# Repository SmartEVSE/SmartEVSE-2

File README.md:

SmartEVSE
=========

Smart Electric Vehicle Charge Controller

# What is it?

It's a open source EVSE (Electric Vehicle Supply Equipment). It supports 1-3 phase charging, fixed charging cable or charging socket. Locking actuator support (3 different types). And it can directly drive a mains contactor for supplying power to the EV. It features a display from which all module parameters can be configured.<br>
Up to 8 modules can be connected together to charge up to eight EV's from one mains connection without overloading it.<br>
The mains connection can be monitored by the (optional) sensorbox or a modbus kWh meter. This allows smart charging.
Communication between the SmartEVSE(s) / Sensorbox or kWh meters is done over RS485(modbus).

The project consists of two parts:
- Smart EVSE controller
- Sensorbox

# Features

- Fits into a standard DIN rail enclosure.
- Measures the current consumption of other appliances, and automatically lowers or increases the charging current to the EV. (sensorbox required)
- The load balancing feature let's you connect up to 8 SmartEVSE's to one mains supply.
- Switched 230VAC output, for contactor/relay.
- Powered RS485 communication bus for sensorbox / Modbus kWh Meters.
- Can be used with fixed cable, or socket and charging cable.
- Automatically selects current capacity of the connected cable (13/16/32A)
- Locking actuator support, locks the charging cable in the socket, automatically unlocks on a power failure.
- RFID reader support, restrict the use of the charging station to max 20 RFID cards.
- An optional modbus kWh meter will measure power and charged energy, and display this on the LCD.
- Built-in temperature sensor.
- All module parameters can be configured using the display and buttons.
- Setup can also be done through serial CLI.
- Firmware upgradable through serial bootloader. 

New V2.20 features are:
- Added EVMETER and EVADR option to the menu. Use a modbus kWh meter to measure the charged energy.
- Added charged energy to the LCD (Smart/Solar mode)
- Uses condensed characters on the LCD, so the 'i' will not use the same space as the 'w'
- Increased the nr of nodes to 7.
- Added RFID reader option. Learn up to 20 RFID cards.

# The Sensorbox

The Sensorbox should be placed where the Mains connection enters the building. Usually just after the kWh meter, this way it will be able to measure the total current per phase and send this information to the SmartEVSE.

In order to measure the current, Current transformers are used. Clip them around the L1,L2 and L3 wires, and plug the other end into the sensorbox.

# Configuring the SmartEVSE

The SmartEVSE has a display, which shows the charging status, and if smart mode is used, also the measured current per phase.
It is possible to configure all settings using the built-in menu.

Three buttons below the display are used for navigating the menu.

Hold the center button for 2 seconds to enter the menu.
You can now use the left and right buttons to go to the different menu options. 

Pressing the center button, selects the option, and allows you change the value (for example change the charging current)

# Building the EVSE

In order to build a complete EVSE (charging station)
you will need:

- SmartEVSE.
- 4 pole NO Contactor rated for the max charging current. (for example Hager ESC440 or ISKRA IKA432-40)
- Fixed charging cable or socket with locking solenoid.
- Enclosure with DIN rail. 
- Terminal blocks (Wago TOPJOB S)

The EVSE needs to be protected with a circuit breaker and residual-current circuit breaker, usually located near or in the distribution board.

# Purchase the SmartEVSE

You can buy a complete assembled SmartEVSEv2 [here](http://www.stegen.com/en/ev-products/66-smart-evse-controller.html)<br>
Information on how to compile and setup the controller can be found on the [smartevse.nl](http://www.smartevse.nl) website.

**The assembled SmartEVSE v2 modules come pre-programmed with the latest firmware (v2.20), and are fully tested!**

# Predefined electric meters

- Sensorbox (1)
- PHOENIX CONTACT EEM-350-D-MCB (2)
- Finder 7E.78.8.400.0212 (3)
- Eastron SDM630 (4)
- ABB B23 212-100 (5)
- SolarEdge SunSpec (6)
- WAGO 879-30x0 (7)
- Finder 7M.38.8.400.0212 (8)
- Custom (9)

# Modbus

Baudrate is 9600bps 8N1 (8bit, no parity bit, one stop bit).
All registers are 16 bit unsigned integers.
Address depends on the Load Balancing configuration:

Load Balancing | Modbus Address
--- | ---
Disabled/Master | 0x01
Node 1 | 0x02
Node 2 | 0x03
Node 3 | 0x04
Node 4 | 0x05
Node 5 | 0x06
Node 6 | 0x07
Node 7 | 0x08

Broadcast to all SmartEVSE with address 0x09.

Modbus register have changed after version 2.20. Use [this readme](https://github.com/SmartEVSE/SmartEVSE-2/tree/b8b6a1a2def22a2bfc3cc30be2f2ef639e2d4389#register-for-external-devices) as reference for version 2.20 or older

## Register 0x00*: EVSE status

Register | Access | Description | Unit | Values
--- | --- | --- | --- | ---
0x0000 | R/W | State | | 0:A / 1:B / 2:C / 3:D / 4:Node request B / 5:Master confirm B / 6:Node request C / 7:Master confirm C / 8:Activation mode / 9:B1 / 10:C1
0x0001 | R/W | Error | Bit | 1:LESS_6A / 2:NO_COMM / 4:TEMP_HIGH / 8:Unused / 16:RCD / 32:NO_SUN
0x0002 | R/W | Charging current | 0.1 A | 0:no current available / 6-80
0x0003 | R/W | EVSE mode (without saving) | | 0:Normal / 1:Smart / 2:Solar
0x0004 | R/W | Solar Timer | s |
0x0005 | R/W | Access bit | | 0:No Access / 1:Access
0x0006 | R/W | Configuration changed (Not implemented) | |
0x0007 | R | Maximum charging current | A |
0x0008 | R/W | Number of used phases (Not implemented) | | 0:Undetected / 1 - 3
0x0009 | R | Real charging current (Not implemented) | 0.1 A |
0x000A | R | Temperature | K |
0x000B | R | Serial number | |
0x0020 - 0x0027 | W | Broadcast charge current. SmartEVSE uses only one value depending on the "Load Balancing" configuration | 0.1 A | 0:no current available

## Register 0x01*: Node specific configuration

Register | Access | Description | Unit | Values
--- | --- | --- | --- | ---
0x0100 | R/W | Configuration | | 0:Socket / 1:Fixed Cable
0x0101 | R/W | Cable lock | | 0:Disable / 1:Solenoid / 2:Motor
0x0102 | R/W | MIN Charge Current the EV will accept | A | 6 - 16
0x0103 | R/W | MAX Charge Current for this EVSE | A | 6 - 80
0x0104 | R/W | Load Balance | | 0:Disabled / 1:Master / 2-8:Node
0x0105 | R/W | External Switch on pin SW | | 0:Disabled / 1:Access Push-Button / 2:Access Switch / 3:Smart-Solar Push-Button / 4:Smart-Solar Switch
0x0106 | R/W | Residual Current Monitor on pin RCM | | 0:Disabled / 1:Enabled
0x0107 | R/W | Use RFID reader | | 0:Disabled / 1:Enabled
0x0108 | R/W | Type of EV electric meter | | *
0x0109 | R/W | Address of EV electric meter | | 10 - 247

## Register 0x02*: System configuration (same on all SmartEVSE in a LoadBalancing setup)

Register | Access | Description | Unit | Values
--- | --- | --- | --- | ---
0x0200 | R/W | EVSE mode | | 0:Normal / 1:Smart / 2:Solar
0x0201 | R/W | EVSE Circuit max Current | A | 10 - 160
0x0202 | R/W | Grid type to which the Sensorbox is connected | | 0:4Wire / 1:3Wire
0x0203 | R/W | CT calibration value | 0.01 | Multiplier
0x0204 | R/W | Max Mains Current | A | 10 - 200
0x0205 | R/W | Surplus energy start Current (per phase) | A | 0 (-16 A) - 32 (+16 A)
0x0206 | R/W | Stop solar charging at 6A after this time | min | 0:Disable / 1 - 60
0x0207 | R/W | Allow grid power when solar charging (sum of phases) | A | 0 (-48 A) - 96 (+48 A)
0x0208 | R/W | Type of Mains electric meter | | *
0x0209 | R/W | Address of Mains electric meter | | 10 - 247
0x020A | R/W | What does Mains electric meter measure | | 0:Mains (Home+EVSE+PV) / 1:Home+EVSE
0x020B | R/W | Type of PV electric meter | | *
0x020C | R/W | Address of PV electric meter | | 10 - 247
0x020D | R/W | Byte order of custom electric meter | | 0:LBF & LWF / 1:LBF &  HWF / 2:HBF & LWF / 3:HBF & HWF
0x020E | R/W | Data type of custom electric meter | | 0:Integer / 1:Double
0x020F | R/W | Modbus Function (3/4) of custom electric meter | |
0x0210 | R/W | Register for Voltage (V) of custom electric meter | | 0 - 65530
0x0211 | R/W | Divisor for Voltage (V) of custom electric meter | 10<sup>x</sup> | 0 - 7
0x0212 | R/W | Register for Current (A) of custom electric meter | | 0 - 65530
0x0213 | R/W | Divisor for Current (A) of custom electric meter | 10<sup>x</sup> | 0 - 7
0x0214 | R/W | Register for Power (W) of custom electric meter | | 0 - 65534
0x0215 | R/W | Divisor for Power (W) of custom electric meter | 10<sup>x</sup> | 0 - 7 /
0x0216 | R/W | Register for Energy (kWh) of custom electric meter | | 0 - 65534
0x0217 | R/W | Divisor for Energy (kWh) of custom electric meter | 10<sup>x</sup> | 0 - 7
0x0218 | R/W | Maximum register read (Not implemented) | |
0x0219 | R/W | WiFi mode | |
0x021A | R/W | Limit max current draw on MAINS (sum of phases) | A | 9:Disable / 10 - 200

 * Number in brackets in section "Predefined electric meters"

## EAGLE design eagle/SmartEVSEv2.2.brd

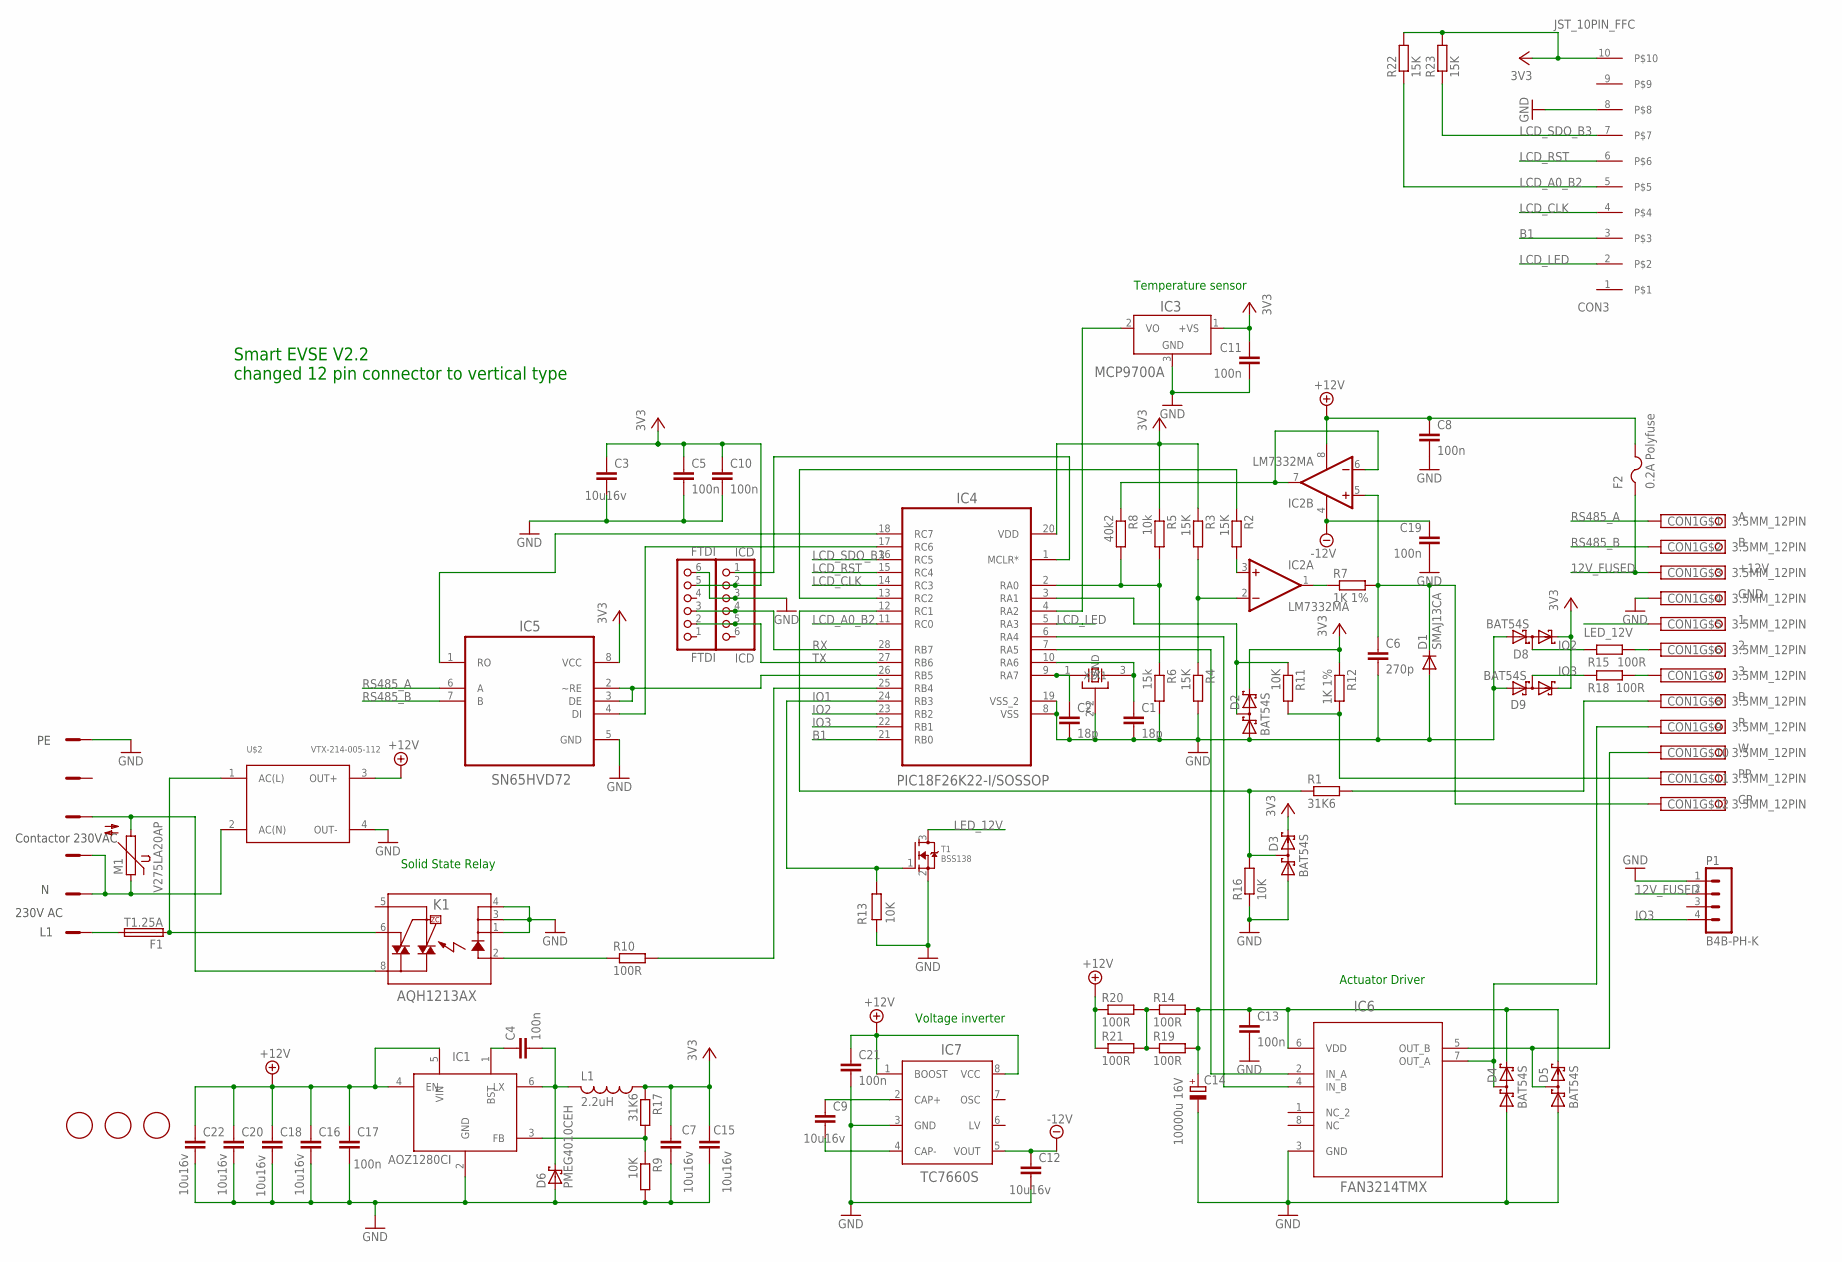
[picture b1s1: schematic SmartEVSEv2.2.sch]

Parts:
C1, C2: 18p; C0603
C3, C7, C9, C12, C15, C16, C18, C20, C22: 10u16v; C0805
C4, C5, C8, C10, C11, C13, C17, C19, C21: 100n; C0603
C6: 270p; C0805
C14: 10000u 16V; EB22,5D
CON1: 3.5MM_12PIN; 12PIN
CON2: DG128-7.5; P_AST027-06
CON3: JST_10PIN_FFC
D1: SMAJ13CA; DO214AC
D2, D3, D4, D5, D8, D9: BAT54S; SOT23
D6: PMEG4010CEH; SOD-123FL
F1: T1.25A; TE5
F2: 0.2A Polyfuse; R1210
FTDI: FTDI; 1X06-BIGLOCK
IC1: AOZ1280CI; SOT23-6
IC2: LM7332MA; SO08
IC3: MCP9700A; SOT23
IC4: PIC18F26K22-I/SOSSOP; SOP65P780X200-28N
IC5: SN65HVD72; SOIC127P600X175-8N
IC6: FAN3214TMX; SOIC127P600X175-8N
IC7: TC7660S; SO08
ICD: ICD; 1X06
K1: AQH1213AX; DIL07SMD
L1: 2.2uH; MCSD43
M1: V275LA20AP; S14K40
P1: B4B-PH-K
Q1: CTS_32X25_SMD; CTS_32X25
R1, R17: 31K6; R0603
R2, R3, R4, R22, R23: 15K; R0603
R5: 10k; R0603
R6: 15k; R0603
R7, R12: 1K 1%; R0603
R8: 40k2; R0603
R9, R11, R13, R16: 10K; R0603
R10, R14, R15, R18, R19, R20, R21: 100R; R0603
T1: BSS138; SOT23
U$1, U$3, U$4: FIDUCIAL; FIDUCIAL_1MM
U$2: VTX-214-005-112

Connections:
12V_FUSED: CON1.3, F2.1, P1.2
+12V: C8.1, C16.1, C17.1, C18.1, C20.1, C21.1, C22.1, F2.2, IC1.4 (EN), IC1.5 (VIN), IC2.8 (V+), IC7.1 (BOOST), IC7.8 (VCC), R20.1, R21.1, U$2.3 (OUT+)
-12V: C12.1, C19.1, IC2.4 (V-), IC7.5 (VOUT)
B1: CON3.3, IC4.21 (RB0)
GND: C1.2, C2.2, C3.2, C5.2, C6.2, C7.1, C8.2, C10.2, C11.2, C12.2, C13.2, C14.-, C15.1, C16.2, C17.2, C18.2, C19.2, C20.2, C21.2, C22.2, CON1.4, CON2.P$6, CON3.8, D1.A, D2.1 (A1), D3.1 (A1), D4.1 (A1), D5.1 (A1), D6.A, D8.1 (A1), D9.1 (A1), FTDI.6, IC1.2 (GND), IC3.3 (GND), IC4.8 (VSS), IC4.19 (VSS_2), IC5.5 (GND), IC6.3 (GND), IC7.3 (GND), ICD.3, K1.1 (K), K1.3 (K1), K1.4 (K2), P1.1, Q1.2 (GND), Q1.4 (GND), R4.2, R6.2, R9.2, R13.1, R16.1, T1.2 (S), U$2.4 (OUT-)
IO1: IC4.24 (RB3), R13.2, T1.1 (G)
IO2: D8.3 (C1A2), IC4.23 (RB2), R15.1
IO3: D9.3 (C1A2), IC4.22 (RB1), P1.4, R18.1
LCD_A0_B2: CON3.5, IC4.11 (RC0), R22.1
LCD_CLK: CON3.4, IC4.14 (RC3)
LCD_LED: CON3.2, IC4.5 (RA3)
LCD_RST: CON3.6, IC4.15 (RC4)
LCD_SDO_B3: CON3.7, IC4.16 (RC5), R23.1
LED_12V: CON1.5, T1.3 (D)
unnamed: D3.3 (C1A2), IC4.12 (RC1), R1.1, R16.2
unnamed: F1.1, K1.6 (DS3), U$2.1 (AC(L))
unnamed: IC4.6 (RA4), IC6.4 (IN_B)
unnamed: IC4.17 (RC6), IC5.4 (DI)
unnamed: IC4.18 (RC7), IC5.1 (RO)
unnamed: C2.1, IC4.9 (RA7), Q1.1 (X1)
unnamed: C1.1, IC4.10 (RA6), Q1.3 (X2)
unnamed: IC2.2 (-IN), R3.2, R4.1
unnamed: C6.1, CON1.12, D1.C, IC2.5 (+IN), R7.2
unnamed: IC4.13 (RC2), R2.1
unnamed: IC2.3 (+IN), R2.2
unnamed: IC4.2 (RA0), R5.2, R6.1, R8.2
unnamed: IC2.1 (OUT), R7.1
unnamed: IC2.6 (-IN), IC2.7 (OUT), R8.1
unnamed: D2.3 (C1A2), IC4.3 (RA1), R11.1
unnamed: C13.1, C14.+, D4.2 (C2), D5.2 (C2), IC6.6 (VDD), R14.2, R19.2
unnamed: IC4.7 (RA5), IC6.2 (IN_A)
unnamed: K1.2 (A), R10.1
unnamed: IC4.25 (RB4), R10.2
unnamed: CON2.P$1, F1.2
unnamed: CON1.11, R11.2, R12.2
unnamed: CON2.P$4, K1.8 (DS1), M1.2
unnamed: IC4.26 (RB5), IC5.2 (~RE), IC5.3 (DE)
unnamed: CON2.P$2, CON2.P$3, M1.1, U$2.2 (AC(N))
unnamed: CON1.9, D4.3 (C1A2), IC6.7 (OUT_A)
unnamed: IC4.1 (MCLR*), ICD.1
unnamed: CON1.10, D5.3 (C1A2), IC6.5 (OUT_B)
unnamed: C4.1, IC1.1 (BST)
unnamed: R14.1, R19.1, R20.2, R21.2
unnamed: CON1.8, R1.2
unnamed: CON1.6, R15.2
unnamed: CON1.7, R18.2
unnamed: C9.1, IC7.2 (CAP+)
unnamed: IC3.2 (VO), IC4.4 (RA2)
unnamed: C9.2, IC7.4 (CAP-)
unnamed: IC1.3 (FB), R9.1, R17.2
unnamed: C4.2, D6.C, IC1.6 (LX), L1.2
RS485_A: CON1.1, IC5.6 (A)
RS485_B: CON1.2, IC5.7 (B)
RX: FTDI.3, IC4.28 (RB7), ICD.4
TX: FTDI.2, IC4.27 (RB6), ICD.5
VCC: C3.1, C5.1, C7.2, C10.1, C11.1, C15.2, CON3.10, D2.2 (C2), D3.2 (C2), D8.2 (C2), D9.2 (C2), FTDI.5, IC3.1 (+VS), IC4.20 (VDD), IC5.8 (VCC), ICD.2, L1.1, R3.1, R5.1, R12.1, R17.1, R22.2, R23.2

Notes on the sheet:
230V AC
Contactor 230VAC
Smart EVSE V2.2 changed 12 pin connector to vertical type
Temperature sensor
Actuator Driver
Solid State Relay
Voltage inverter
GND
+12V

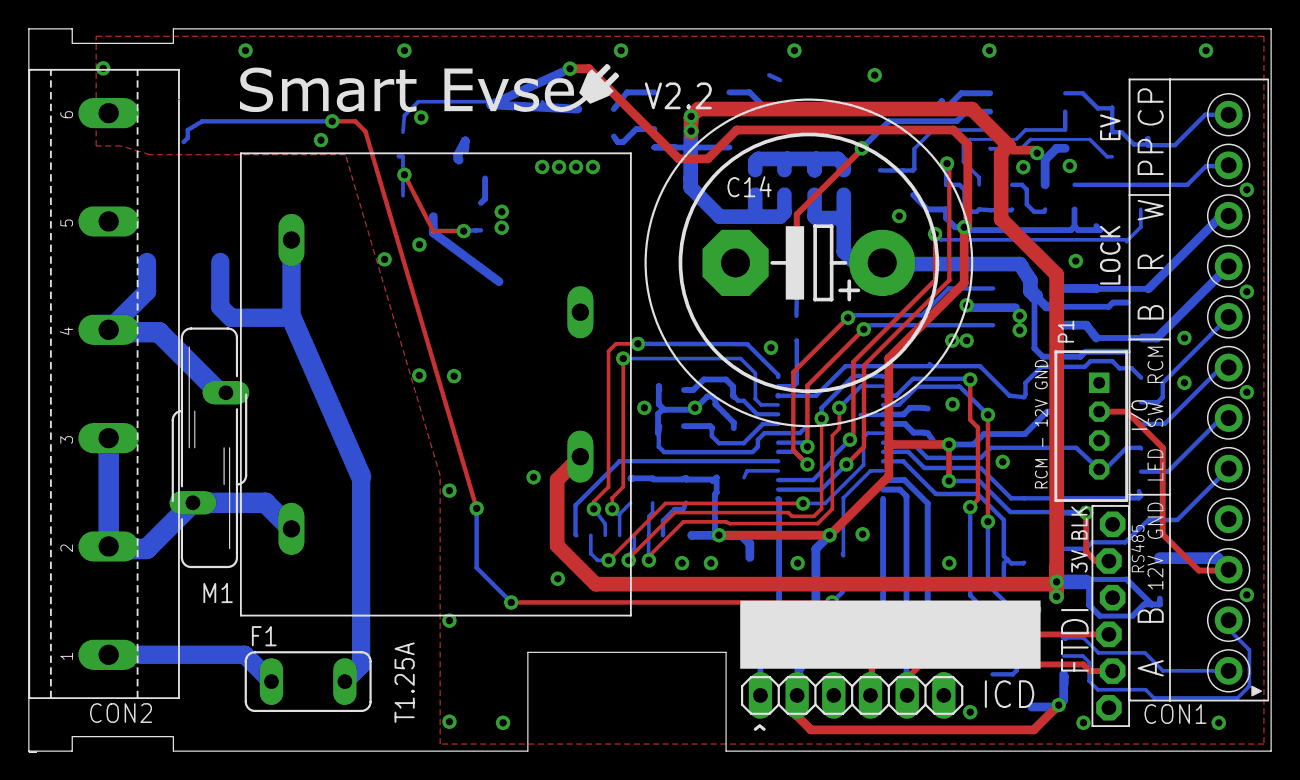
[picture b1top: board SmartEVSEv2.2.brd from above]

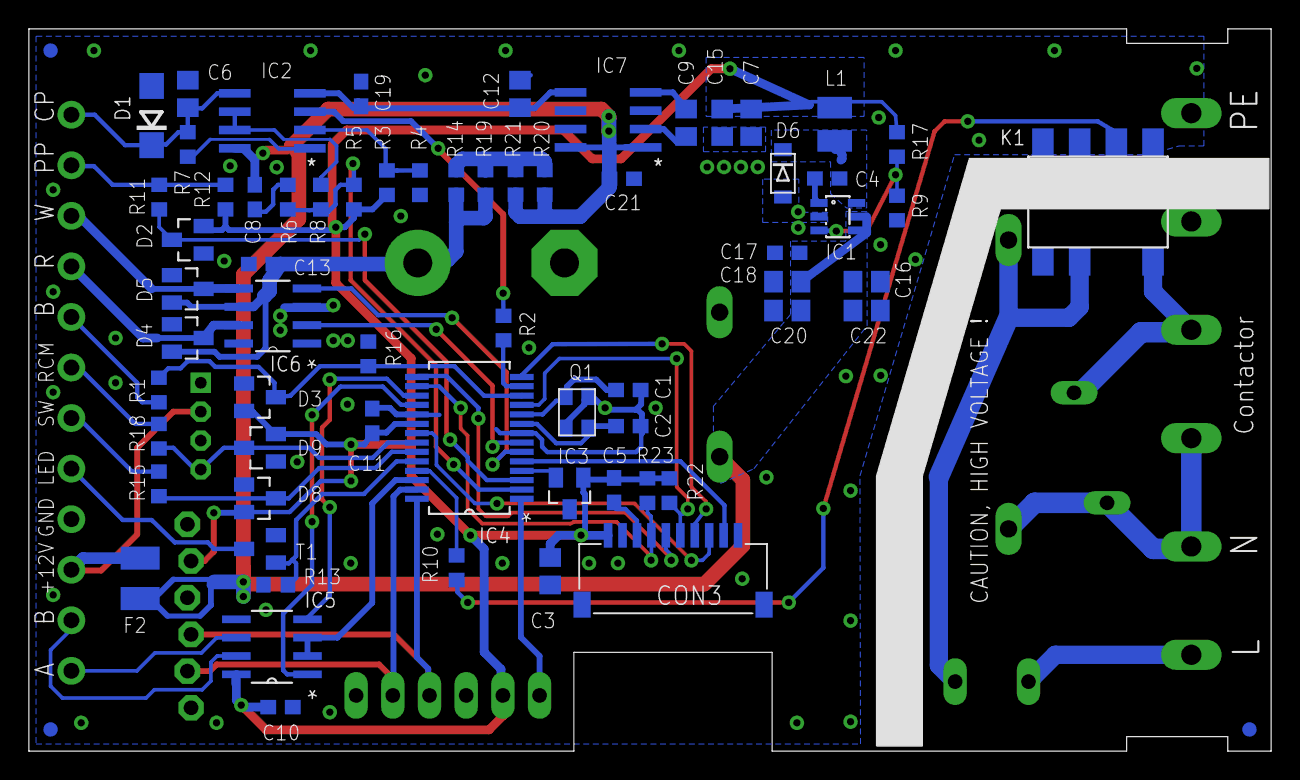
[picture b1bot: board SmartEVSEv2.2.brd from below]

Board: 2 copper layers, 86.0 x 50.0 mm, 77 parts (68 on the bottom side), 56 nets.

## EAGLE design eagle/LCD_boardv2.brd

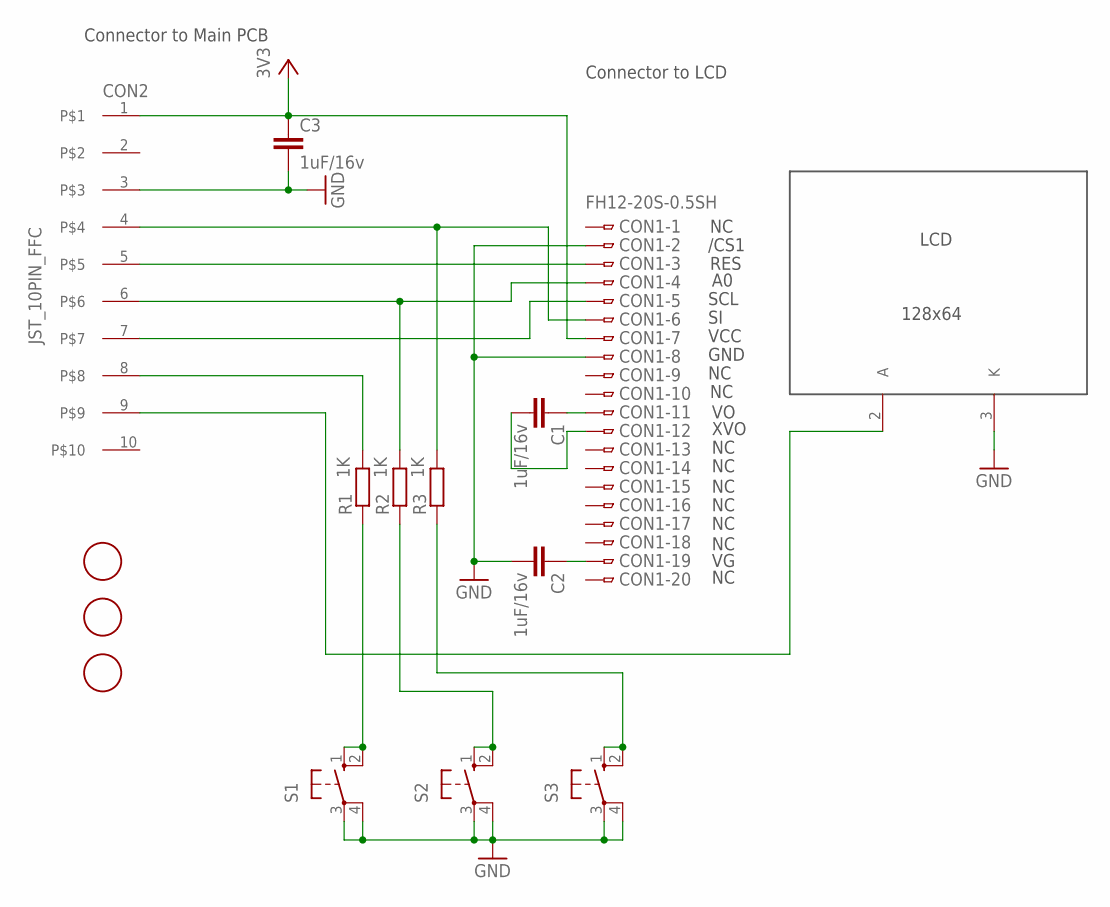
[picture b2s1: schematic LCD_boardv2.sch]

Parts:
C1, C2, C3: 1uF/16v; C0805
CON1: FH12-20S-0.5SH
CON2: JST_10PIN_FFC
R1, R2, R3: 1K; R0603
S1, S2, S3: 10-XX; B3F-10XX
U$1: LCD_DEM128064
U$2, U$3, U$4: FIDUCIAL; FIDUCIAL_1MM

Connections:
GND: C2.2, C3.2, CON1.2, CON1.8, CON2.3, S1.3, S1.4 (P1), S2.3, S2.4 (P1), S3.3, S3.4 (P1), U$1.3 (K)
unnamed: C1.1, CON1.11
unnamed: C1.2, CON1.12
unnamed: C2.1, CON1.19
unnamed: CON1.6, CON2.4, R3.2
unnamed: CON1.3, CON2.5
unnamed: CON1.4, CON2.6, R2.2
unnamed: CON1.5, CON2.7
unnamed: R1.1, S1.1 (S), S1.2 (S1)
unnamed: CON2.9, U$1.2 (A)
unnamed: R2.1, S2.1 (S), S2.2 (S1)
unnamed: CON2.8, R1.2
unnamed: R3.1, S3.1 (S), S3.2 (S1)
VCC: C3.1, CON1.7, CON2.1

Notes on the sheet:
/CS1
RES
SCL
VCC
GND
XVO
Connector to Main PCB
Connector to LCD

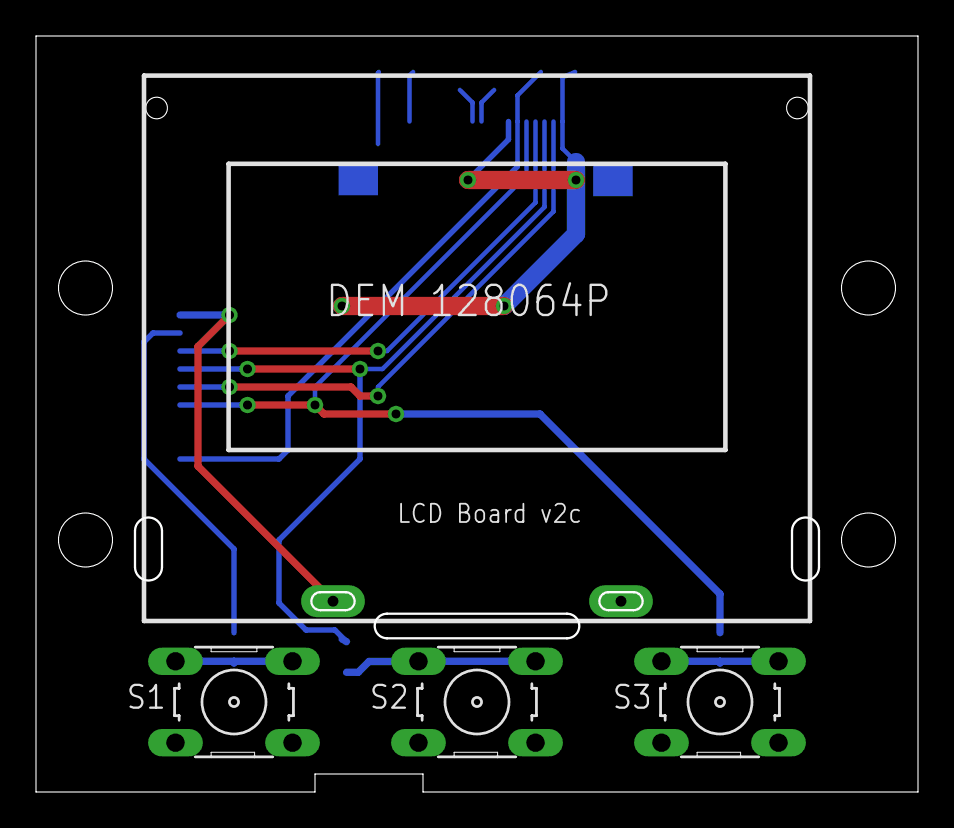
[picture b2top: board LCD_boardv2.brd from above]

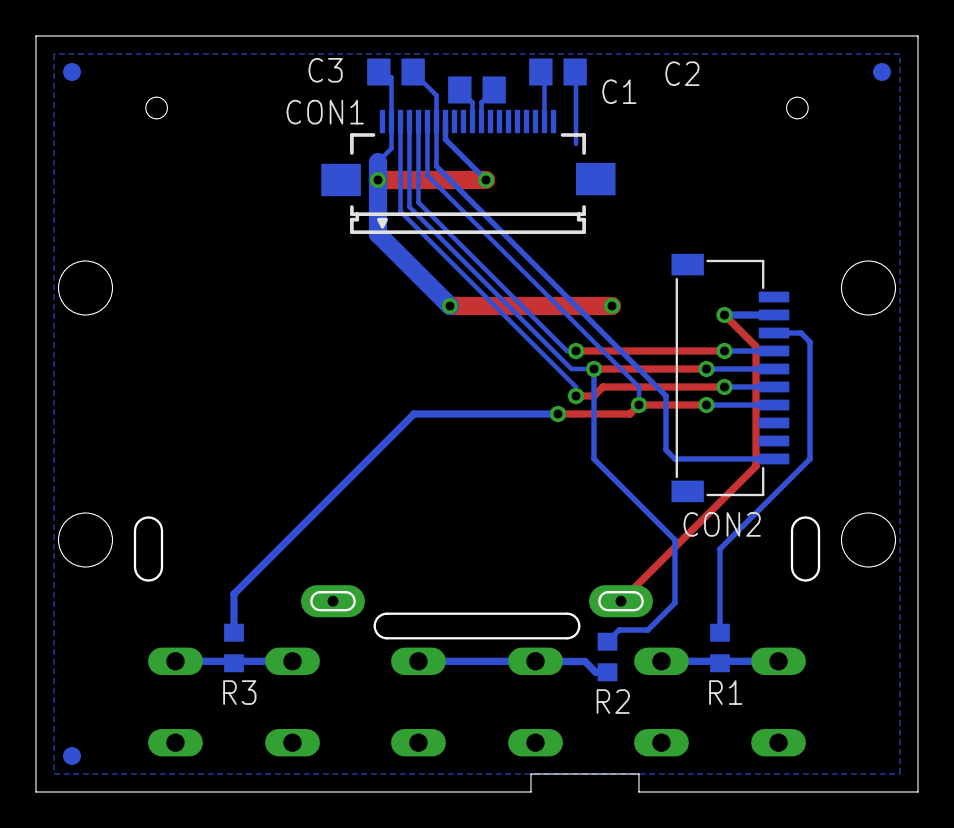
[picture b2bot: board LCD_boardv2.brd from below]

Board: 2 copper layers, 48.9 x 41.9 mm, 15 parts (11 on the bottom side), 14 nets.

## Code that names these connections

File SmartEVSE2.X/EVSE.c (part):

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            // fall through
        case STATE_A:                                                           // State A1
            CCP1CON = 0;                                                        // PWM off
            PORTCbits.RC2 = 1;                                                  // Control pilot static +12V (or +9V if connected to EV)
            CONTACTOR_OFF;                                                      // Contactor OFF
            if (NewState == STATE_A) {
                Error &= ~NO_SUN;
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        delay(3000);                                                            // wait 3 seconds for capacitor to charge

        CCP1CON = 0;                                                            // PWM off
        PORTCbits.RC2 = 0;                                                      // Control pilot static -12V
        delay(100);                                                             // wait 100 msec
        if (ReadPilot() == PILOT_DIODE) TestState = STATE_B;                    // should be -12V
        else error = 1;
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        TRISB = 0b10000101;                                                     // RB7(RX2), RB0,2 inputs. all other output
        LATBbits.LATB1 = 1;                                                     // set IO3 to high
        delay(5000);                                                            // wait 5 seconds for capacitor to charge
        if (PORTCbits.RC1 == 1) error ^= 4;                                     // error, Solenoid not activated !

        delay(10);
                                                                                // Contactor + I/O test
        if (PORTBbits.RB2 == 1)                                                 // sample input PIN IO2
        {
            LATBbits.LATB1 = 0;
            delay(10);
            if (PORTBbits.RB2 != 0) error ^= 8;                                 // error
        } else error ^= 8;                                                      // error

        TestState = STATE_CB;
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    } else if (TestState == STATE_CB && State == STATE_B) {
        TRISB = 0b10000001;                                                     // RB7(RX2), RB0 inputs. all other output
        delay(1000);
        if (PORTCbits.RC1 == 0) error ^= 4;                                     // Solenoid FAIL!!
        else if (!error) {
            TestState = 80;
            Lock = 0;
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    PMD2 = 0b00000000;

    PORTA = 0;                                                                  // Init PORTA
    ANSELA = 0b00000111;                                                        // RA0, RA1, RA2 are analog inputs (pin 2,3,4)
    TRISA = 0b00000111;                                                         // Set RA0,RA1,RA2 as inputs

    PORTB = 0;
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
        BlinkLed();                                                             // Handle the blinking of the 12V LED

        TRISC = 0b10100011;                                                     // Set RC5 and RC0 to input. Make sure there are pull-ups on these pins.
        NOP();
        NOP();
        x = (PORTC & 0b00100001);                                               // Read Two Button Inputs on RC5(>) and RC0(select)
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
        if (RCmon == 1 && PORTBbits.RB1 == 1)                                   // RCD monitor active, and RCD DC current > 6mA ?
        {
           if (PORTBbits.RB1 == 1) {                                            // check again, to prevent voltage spikes from tripping the RCD detection (2.07)
                if (State) setState(STATE_B1);
                Error = RCD_TRIPPED;
                LCDTimer = 0;                                                   // display the correct error message on the LCD
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                        setState(STATE_ACTSTART);
                        ActivationTimer = 3;
                        CCP1CON = 0;                                            // PWM off
                        PORTCbits.RC2 = 0;                                      // Control pilot static -12V
                    }
                    NextState = NOSTATE;                                        // no State to switch to
                }
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
        if (State == STATE_ACTSTART && ActivationTimer == 0) {
            setState(STATE_B);                                                  // Switch back to State B
            PORTCbits.RC2 = 1;                                                  // Control pilot static +12V
            ActivationMode = 255;                                               // Disable ActivationMode
        }

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
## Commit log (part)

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2017-08-28 Smart EVSE v2 code and pcb files
2018-05-16 v2.03 Changed lowest MaxMains setting to 10A
2019-02-24 typo
2019-04-24 Version 2.05 + 2.06
    2.05 Fix: Using a 16A charge cable would limit MaxCurrent to 16A, until a reset of the module or adjusting the MAX value using the menu.
    Fix: Increased number of times a STATE change needs to be valid, before the actual STATE change takes place.
    LCD Backlight will now be activated on any key press, and will turn off after 30 seconds of inactivity (except when charging).
    CT's default values can be restored by holding both < and > keys while in the CAL menu.
    RCMON menu option added. This adds support for DC Residual Current sensors, as required by IEC62955.
    IO3 is used as the fault input (active high).
2019-05-26 Add Solar mode and animated graphic
2019-05-26 Simplify GLCDMenu by creating a MenuItems array and navigate through the array
2019-05-27 Create function getMenuItemOption to get active option of an menu entry for use in RS232cli and GLCDMenu
2019-05-28 Some cleanups
2019-05-29 Bugfixes - Move U1packet buffer into main loop - Modbus packet length check - Modbus request response detection - Reset no communication timer on broadcast receive
2019-05-30 Bugfix: Send Modbus Requests only on Load Balancing: Disabled or Master
2019-05-30 Change broadcast address back to 0x00
2019-06-01 Switch modbus receive packets from SmartEVSE in 3 categories: DataReceived = 1 : Measurement from electric meter DataReceived = 2 : Communication from Master to Slave DataReceived = 3 : Communication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
2019-06-02 Modbus implementation to read and set configuration options: Register 0xC*: Configuration 0xC0: CONFIG 0xC1: MODE 0xC2: START 0xC3: STOP 0xC4: LOADBL 0xC5: MIN 0xC6: CABLE 0xC7: LOCK 0xC8: ACCESS 0xC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
2019-06-03 Modbus read status values: 0xA0: State 0xA1: Error 0xA2: Charging current
2019-06-03 Bugfix: Do not show help on EXIT MENU
2019-06-04 Create function "updateCurrentData" for processing received current measurement
2019-06-05 Bugfix: Disable receive of Mains electric meter packets if mode is normal Bugfix: Sync MODE and MAX with slaves
2019-06-07 Create struct EMConfig to store EM configurations. - Renumber EM IDs to simplify code - Remove EM option "Disabled" as it is mandatory
2019-06-09 Add possibility to configure custom electric meter
2019-06-10 Validate settings before save and after read
2019-06-10 Bugfix: Use variable CT1 in GLCD sensorbox calibration instead of ICal
2019-06-12 Define IsetBalance as signed int as it can get negative
2019-06-13 Wait for IO2 state change until trigger action
2019-06-14 Add Switch option "Smart-Solar" to choose with an external switch between smart and solar charging Rename Access variable/constant to Switch
2019-06-15 For switch mode Smart-Solar device must be in Solar mode
2019-06-15 Add Switch IO2 option for Access Switch and Smart-Solar Push-Button
2019-06-15 Enable custom electric meter divisor from 100000 to 10000000
2019-06-15 Save litte memory by using an array for Load Balancing option strings
2019-06-16 Bugfix in Modbux FC=16 write multiple
2019-06-16 Always show config option "MAX" as it can also limit current on Slave EVSE
2019-06-19 Eastron SDM630 current is unsigned -> Get sign from power register
2019-06-20 Remove double check of ISRTXFLAG in RS485SendBuf
2019-06-20 Change EMConfig.IRegister type to unsigned int as EMConfig.ERegister
2019-06-20 Sensorbox calibration bugfixes
2019-06-20 Add visualisation for solar mode and solar stop timer
2019-06-21 Reordered modbus state variables to bundle load balancing relevant information
2019-06-25 Remove Sensorbox 1 configuration option
2019-07-10 Show "Disable" instead of "0 min" on solar stop time
2019-07-24 Check modbus register in response of electric meter
2019-10-29 Master/Slave bugfixes, Circuit option added
    Cable option removed, replaced with Circuit option.
    Switching between Solar/Smart mode with left button on SmartEVSE module
2019-11-08 Updated Schematics
    Updated schematic and board to version 2.2
2019-11-15 Updated manual to v1.11
    Updated Smart EVSE install manual to v1.11 for firmware version 2.10
2020-01-26 Version 2.13 Master/Slave communication bug fixes.
    Various Master/Slave communication bug fixes.
    created utils/bootloader/math.c files, as the main sourcefile became too large
2020-01-26 Master/Slave communication bug fixes.
    Various Master/Slave communication bug fixes.
    created utils/bootloader/math.c files, as the main sourcefile became too large
2020-06-04 version 2.16 Added Import / Grid menu option, bugfixes
    2.15 Added check to see if Sensorbox data contains new measurement data.
    - Added IMPORT menu option, which allows for power import from the grid when solar charging.
    - Added compile time option to compensate for 230V-400V transformers.
    - Added Activation mode, which is triggered if state C is not entered within 30 seconds.
    - If an external push button is used as Smart/Solar mode switch, holding this button for 1.5 seconds will now stop charging.
    2.16 Fixed Smart/Solar mode switch, it would force Solar or Smart mode, even in Normal mode.
2020-06-08 version 2.17 Solar mode state switch bugfix. Hides the CAL menu when not used
    Fixed state switch bug while in solar mode.
    Hides CAL menu option when CT's are not used.
2020-06-26 Make Modbus Register 0xA6 Charging current writeable
2020-10-20 Update comments of *Meter variables
2020-10-20 Show PV meter address option only if PV meter selected
2020-10-20 Remove ERegCount from EMConfig (Energy is stored most times in two bytes, more bytes not manageable)
2020-10-20 Initialize CalActive = 0 in receiveCurrentMeasurement
2020-10-22 Rename function GLCD_print2 to GLCD_print_buf2
2020-10-23 - Remove leading zeros - Round measured values - Condense font
2020-10-23 - Add EV meter option - Display charged amount of energy
2020-10-25 Center message "READY" with chargedelay
2020-10-25 Cleanup function GLCD
2020-11-25 Simplify functions pow10 and sprintfd
2020-11-30 GLCD cleanup
2020-12-01 Read serial number from flash
2020-12-01 Added setup menu navigation indicator
2020-12-02 Added RFID reader option
2020-12-02 Use constants for minimum and maximum modbus address of electric meter
2020-12-02 Declare variable at top of function crc16
2020-12-03 Extend EMConfig struct with Modbus function and voltage register information
2020-12-06 Extend custom electric meter configuration (add option for voltage, power and energy, and allow registers up to 65535)
2020-12-06 Update position of "kwh" and the menu arrow "<"
2020-12-06 Auto repeat button press when holding it down
2020-12-12 Define log levels
2020-12-12 Save 184 program bytes in function receiveCurrentMeasurement
2020-12-23 Change broadcast address, remove stateB in SlaveState handler
2020-12-23 Change files EVSE.* and GLCD.* to UNIX line endings
2020-12-24 Update documentation
2020-12-24 Optimize calculation with separate PV electic meter
2020-12-24 Move function GetPosInMenu to GLCD.c
2020-12-25 Enable EV electric meter for all SmartEVSE nodes
2020-12-25 Rename "Slave" to "Node"
2020-12-27 Move new line character in LOG_* printf to the beginning
2021-01-14 Optimize EV electric meter poll
2021-01-14 Don't response on broadcast and save some program bytes
2021-01-14 Show real charging power in Smart/Solar mode
2021-01-15 Switch on backlight when removing charging cable
2021-01-15 Use STATE constants for BalancedState
2021-01-16 Simplify GLCD text rotation and add charging power
2021-01-22 Save 58 program bytes
2021-01-22 Make the Solar Stop timer work on nodes
2021-01-22 Bugfix: Extend Str in GLCD to 11 chars
2021-01-23 Use modbus status register for broadcast error and solar timer
2021-01-27 Broadcast is always a request
2021-01-28 Use signed int/long instead of signed double for all current calculations
2021-01-28 Filter only Sensorbox from EV electric meter
2021-01-28 Cleanup file header include
2021-01-28 Create extra files for OneWire / RFID code
2021-02-06 fix TestIO
2021-02-11 updated manual and readme
    Updated manual to v2.20
2021-02-12 Set modbus address 0x01 when load balancing is disabled
2021-02-13 Define modbus buffer size with a constant
2021-02-13 Create setMode function
2021-03-30 Transmit EV electric meter configuration only when changed
2021-04-03 Link to old modbus register reference
2021-04-04 16MHz INTOSC fallabck (IESO=ON)
2021-04-04 Support for SolarEdge Inverter in SunSpec mode as MAINS power meter
2021-04-05 Solving (all but 1) level -2 parser/compiler errors
    Removed all "far" qualifiers as per
    MPLAB® C18 to XC8 C Compiler
    Migration Guide, section 3.9.1 and 3.10.1
    Altered few data types / typecasts
    Code now compiles with just 1 warning (765) on line 625 of modbus.c on XC8 Compiler Warning level -2
    Code compiled successfully with
2021-04-08 MCLRE = INTMCLR
2021-04-08 Update EVSE.c
    Reverted the removal of "unsigned" on char LCDpos, following comment mstegen
    Updated comment on static unsigned char Str[10]; as per comment maximevince
2021-04-12 Update Charge current broadcast documentation
2021-04-17 Fix int cast for Irms[x]
2021-05-10 Allow custom meter FUNCTION config
2021-05-11 Support for SolarEdge Inverter in SunSpec mode
2021-05-13 Solved some "implicit signed to unsigned conversion" compiler warnings
2021-05-16 Change receiveMeasurement function to use number of values instead of position in the buffer to save some program memory
2021-06-28 Add WAGO electric meter
2021-11-02 Add option to use one RFID card to unlock/lock the EVSE
2021-11-10 Save some program bytes
2021-11-26 Compare start current value with sum of available current
2021-12-10 Automatic start current
2021-12-10 Add compile flag to import current only when minimum current is not available
2022-01-01 Reduce font array and save 690 byte program memory
2022-01-01 Use two dimensional font array
2022-01-02 Add additional parameter "options" in GLCD_write_buf: - Merge character with the background - Shift character 0-7 pixel down for exact placement
2022-01-03 Add compile option to use full ISO 8859-15 charset
2022-01-06 Fix StartCurrent detection with shared EV electric meter
2022-01-07 Move actions to setState function
2022-01-07 Move font to font5x8.c
2022-01-25 Visualize STATE_A (EV disconnected)
2022-02-25 WiFi option for Sensorbox 2
2022-02-28 Implement state C1
2022-03-01 Create setAccess function
2022-03-06 Show state name in debug output
2022-03-08 Update menu navigation counter when changing options
2022-05-25 Only the Master should process responses from a Node
2022-06-04 Allow Smart/Solar switch on a node
2022-06-17 Increase external button bounce delay
2022-06-17 Try to broadcast communication error to Nodes
2022-06-28 Allow mode change within the menu of the master controller when nodes are active
2022-06-30 Increase SolarStopTimer when measurement is not finished
2022-07-03 Remove ResetBalancedStates and reset node state when node goes offline
2022-07-03 Change EMConfig xDivisor to signed char
2022-07-05 Changing MaxCurrent on a node should change ChargeCurrent
2022-07-10 Automatic StartCurrent detection only in solar mode
2022-07-10 On automatic StartCurrent detection pause SolarStopTimer and print "DETECT" instead of the time
2022-07-11 Move automatic StartCurrent detection into SOLAR_MODE block
2022-07-12 Change ChargeTimer to ChargeDelay
2022-07-17 Show number of phases detected with Mains electric meter on Node
2022-07-17 Delay with minimum current when start solar charging
2022-08-08 Update Modbus State documentation
2022-08-19 Use function for phase detection
2022-08-24 Change StartCurrent trigger
2022-08-24 Stop StartCurrent detection when car is unplugged while detecting
2022-08-24 Change phase detection to measure 3 times the same number of used phases
2023-03-17 Don't write SolarStopTimer and DETECT at the same time on the display
2023-05-03 Add compile flag IMPORTCURRENT_SUM
2023-05-22 Set unused bytes on dataType MB_DATATYPE_INT16 in combineBytes
2024-03-10 Dynamic decimal point on kWh information
2024-11-17 Revert "Add compile flag IMPORTCURRENT_SUM"
    This reverts commit a58c5cc8a43e6416b9944f0efc9aade767d5cdab.
2024-11-17 Allow ImportCurrent to be negative (for steady export)
2024-11-17 Allow StartCurrent to be negative
2024-11-17 Stop solar charging only when over 6 A (per phase) more than StartCurrent is used
2024-11-17 Correct call of sprintf

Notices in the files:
SmartEVSE2.X/EVSE.c:
(C) 2013-2022  Michael Stegen / Stegen Electronics
parts and their libraries:
con-jst-ph: Copyright (C) 2016, Bob Starr
